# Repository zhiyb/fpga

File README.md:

# fpga
FPGA (DE0-Nano) attachment PCB designs for fun

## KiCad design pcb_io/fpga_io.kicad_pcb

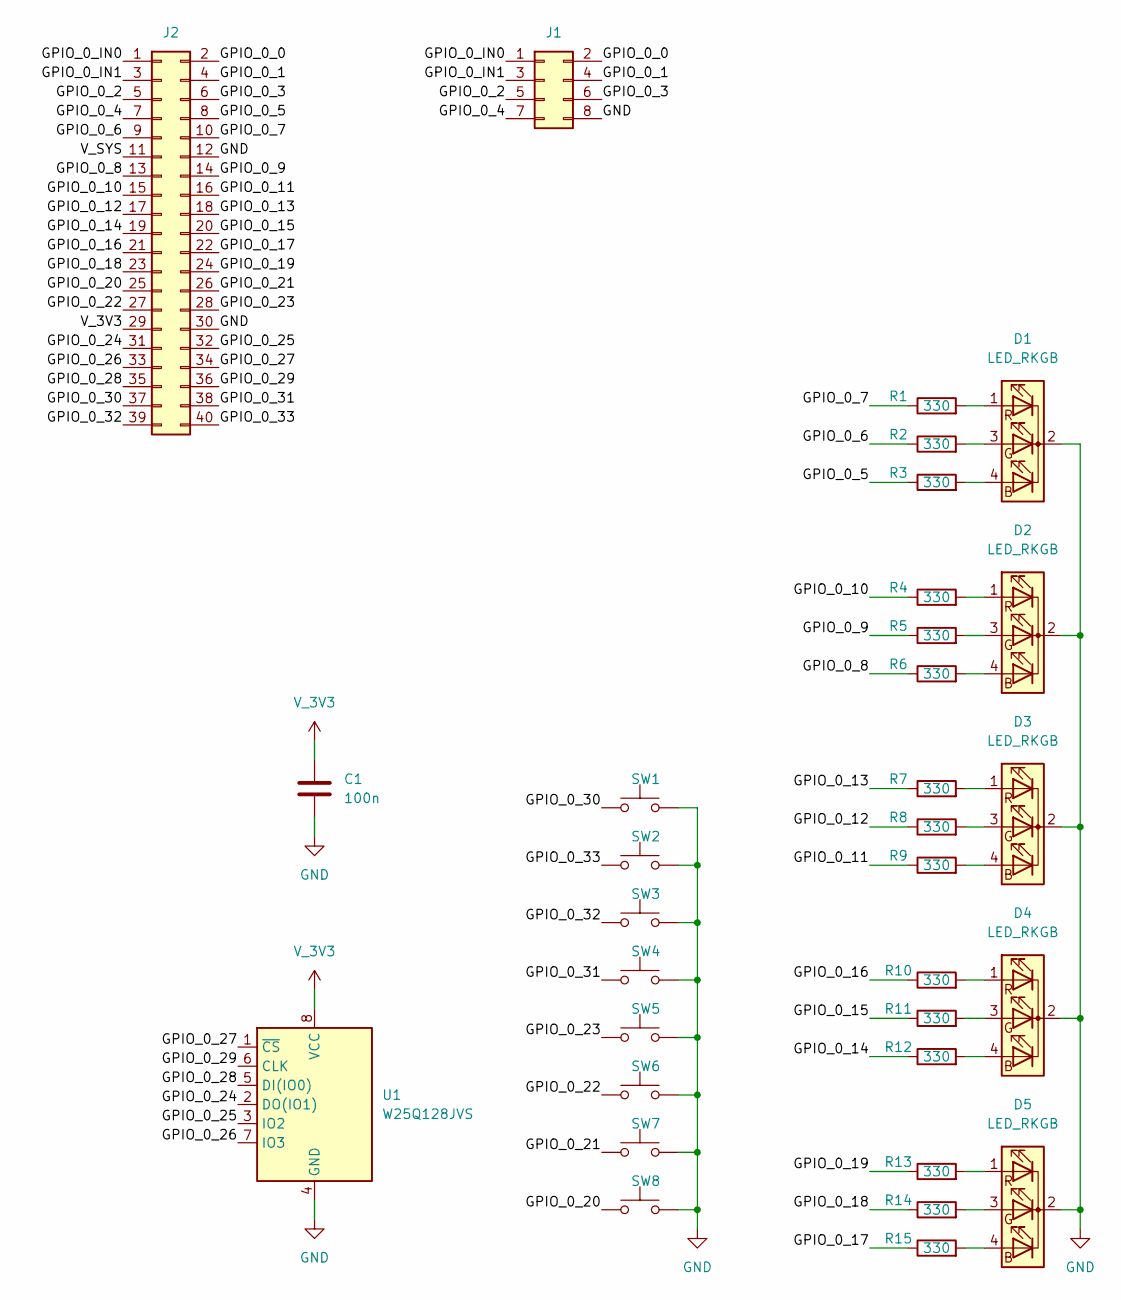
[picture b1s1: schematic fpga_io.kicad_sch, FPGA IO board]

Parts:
C1: 100n; C_0603_1608Metric
D1, D2, D3, D4, D5: LED_RKGB; LED_D5.0mm-4_RGB
J1: Conn_02x04_Odd_Even; PinHeader_2x04_P2.54mm_Vertical
J2: Conn_02x20_Odd_Even; PinSocket_2x20_P2.54mm_Vertical
R1, R2, R3, R4, R5, R6, R7, R8, R9, R10, R11, R12, R13, R14, R15: 330; R_0805_2012Metric
SW1, SW2, SW3, SW4, SW5, SW6, SW7, SW8: SW_Push; SW_Push_1P1T_NO_6x6mm_H9.5mm
U1: W25Q128JVS; SOIC-8_5.23x5.23mm_P1.27mm

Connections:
/GPIO_0_0: J1.2, J2.2
/GPIO_0_1: J1.4, J2.4
/GPIO_0_2: J1.5, J2.5
/GPIO_0_3: J1.6, J2.6
/GPIO_0_4: J1.7, J2.7
/GPIO_0_5: J2.8, R3.1
/GPIO_0_6: J2.9, R2.1
/GPIO_0_7: J2.10, R1.1
/GPIO_0_8: J2.13, R6.1
/GPIO_0_9: J2.14, R5.1
/GPIO_0_10: J2.15, R4.1
/GPIO_0_11: J2.16, R9.1
/GPIO_0_12: J2.17, R8.1
/GPIO_0_13: J2.18, R7.1
/GPIO_0_14: J2.19, R12.1
/GPIO_0_15: J2.20, R11.1
/GPIO_0_16: J2.21, R10.1
/GPIO_0_17: J2.22, R15.1
/GPIO_0_18: J2.23, R14.1
/GPIO_0_19: J2.24, R13.1
/GPIO_0_20: J2.25, SW8.1
/GPIO_0_21: J2.26, SW7.1
/GPIO_0_22: J2.27, SW6.1
/GPIO_0_23: J2.28, SW5.1
/GPIO_0_24: J2.31, U1.2 (DO(IO1))
/GPIO_0_25: J2.32, U1.3 (IO2)
/GPIO_0_26: J2.33, U1.7 (IO3)
/GPIO_0_27: J2.34, U1.1 (~CS)
/GPIO_0_28: J2.35, U1.5 (DI(IO0))
/GPIO_0_29: J2.36, U1.6 (CLK)
/GPIO_0_30: J2.37, SW1.1
/GPIO_0_31: J2.38, SW4.1
/GPIO_0_32: J2.39, SW3.1
/GPIO_0_33: J2.40, SW2.1
/GPIO_0_IN0: J1.1, J2.1
/GPIO_0_IN1: J1.3, J2.3
/V_SYS: J2.11
GND: C1.2, D1.2 (K), D2.2 (K), D3.2 (K), D4.2 (K), D5.2 (K), J1.8, J2.12, J2.30, SW1.2, SW2.2, SW3.2, SW4.2, SW5.2, SW6.2, SW7.2, SW8.2, U1.4 (GND)
unnamed: D1.4 (BA), R3.2
unnamed: D1.3 (GA), R2.2
unnamed: D1.1 (RA), R1.2
unnamed: D2.4 (BA), R6.2
unnamed: D2.3 (GA), R5.2
unnamed: D2.1 (RA), R4.2
unnamed: D3.4 (BA), R9.2
unnamed: D3.3 (GA), R8.2
unnamed: D3.1 (RA), R7.2
unnamed: D4.4 (BA), R12.2
unnamed: D4.3 (GA), R11.2
unnamed: D4.1 (RA), R10.2
unnamed: D5.4 (BA), R15.2
unnamed: D5.3 (GA), R14.2
unnamed: D5.1 (RA), R13.2
V_3V3: C1.1, J2.29, U1.8 (VCC)

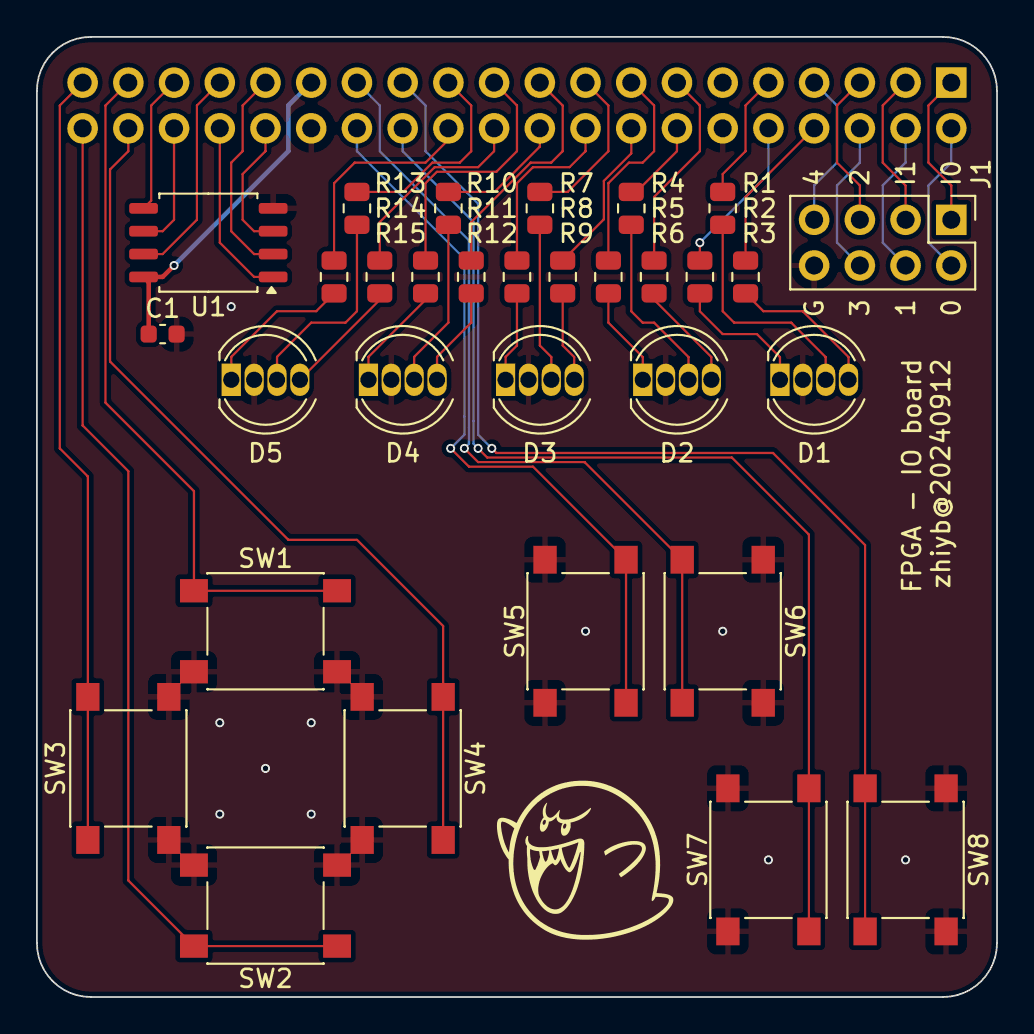
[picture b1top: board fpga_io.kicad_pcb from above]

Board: 2 copper layers, 53.3 x 53.3 mm, 32 parts (1 on the bottom side), 53 nets.

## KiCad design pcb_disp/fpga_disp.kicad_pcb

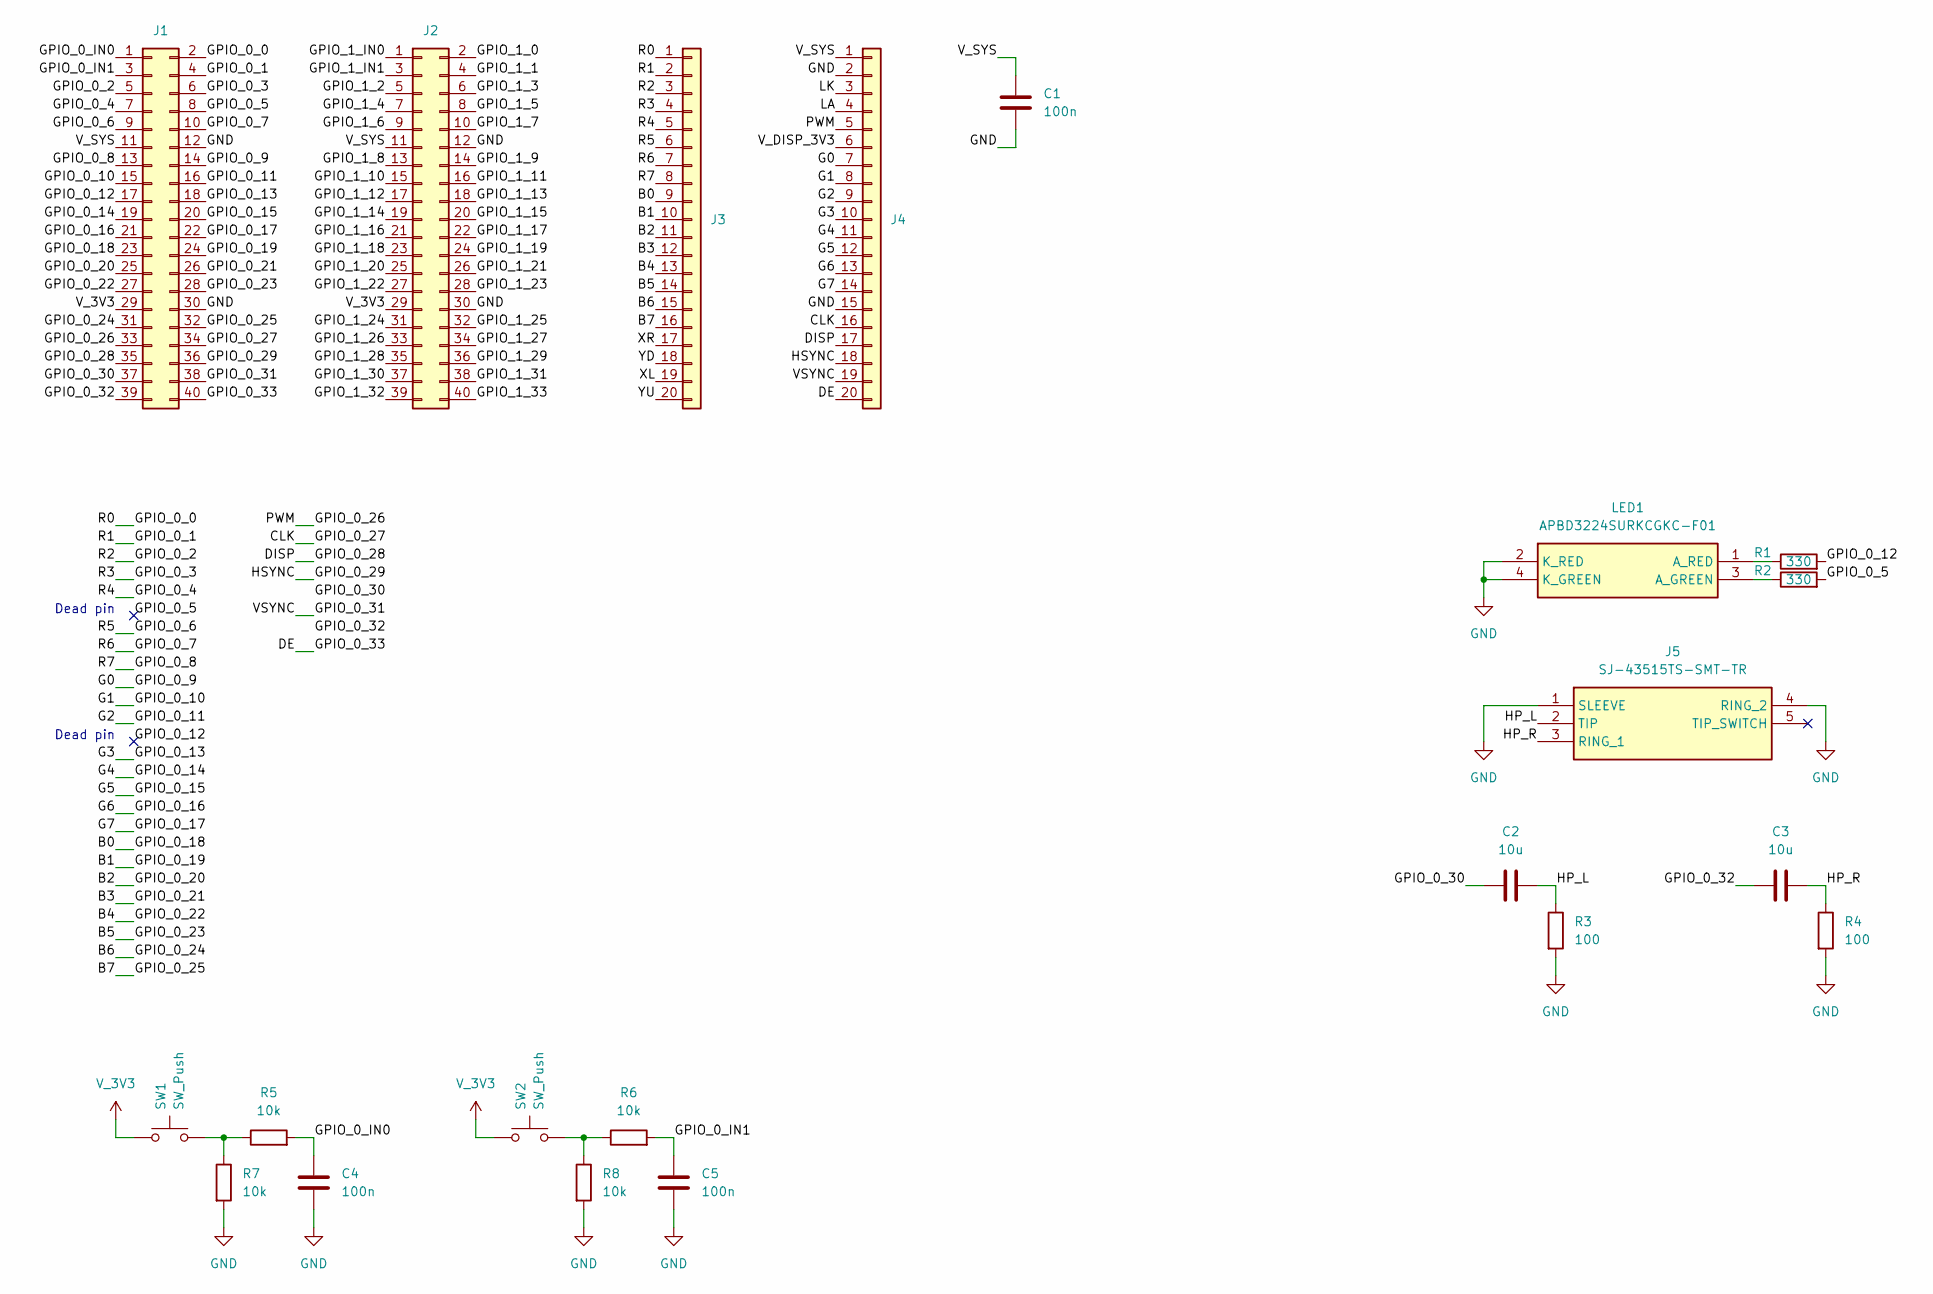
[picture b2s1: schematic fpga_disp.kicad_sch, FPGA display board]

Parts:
C1, C4, C5: 100n; C_0603_1608Metric
C2, C3: 10u; C_0805_2012Metric
J1, J2: Conn_02x20_Odd_Even; PinSocket_2x20_P2.54mm_Vertical
J3, J4: Conn_01x20; PinHeader_1x20_P2.54mm_Vertical
J5: SJ-43515TS-SMT-TR; SJ43515TSSMTTR; Mouser Part Number 490-SJ43515TS-SMT-TR
LED1: APBD3224SURKCGKC-F01; APBD3224SURKCGKCF01; Mouser Part Number 604-APBD3224SURKCGKC
R1, R2: 330; R_0805_2012Metric
R3, R4: 100; R_0805_2012Metric
R5, R6, R7, R8: 10k; R_0805_2012Metric
SW1, SW2: SW_Push; SW_Push_1P1T_NO_6x6mm_H9.5mm

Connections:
/B0: J1.23, J3.9
/B1: J1.24, J3.10
/B2: J1.25, J3.11
/B3: J1.26, J3.12
/B4: J1.27, J3.13
/B5: J1.28, J3.14
/B6: J1.31, J3.15
/B7: J1.32, J3.16
/CLK: J1.34, J4.16
/DE: J1.40, J4.20
/DISP: J1.35, J4.17
/G0: J1.14, J4.7
/G1: J1.15, J4.8
/G2: J1.16, J4.9
/G3: J1.18, J4.10
/G4: J1.19, J4.11
/G5: J1.20, J4.12
/G6: J1.21, J4.13
/G7: J1.22, J4.14
/GPIO_0_0: J1.2, J3.1
/GPIO_0_1: J1.4, J3.2
/GPIO_0_2: J1.5, J3.3
/GPIO_0_3: J1.6, J3.4
/GPIO_0_4: J1.7, J3.5
/GPIO_0_5: J1.8, R2.2
/GPIO_0_6: J1.9, J3.6
/GPIO_0_7: J1.10, J3.7
/GPIO_0_8: J1.13, J3.8
/GPIO_0_12: J1.17, R1.2
/GPIO_0_26: J1.33, J4.5
/GPIO_0_29: J1.36, J4.18
/GPIO_0_30: C2.1, J1.37
/GPIO_0_31: J1.38, J4.19
/GPIO_0_32: C3.1, J1.39
/GPIO_0_IN0: C4.1, J1.1, R5.2
/GPIO_0_IN1: C5.1, J1.3, R6.2
/HP_L: C2.2, J5.2 (TIP), R3.1
/HP_R: C3.2, J5.3 (RING_1), R4.1
/LA: J4.4
/LK: J4.3
/V_DISP_3V3: J4.6
/V_SYS: C1.1, J1.11, J2.11, J4.1
/XL: J3.19
/XR: J3.17
/YD: J3.18
/YU: J3.20
GND: C1.2, C4.2, C5.2, J1.12, J1.30, J2.12, J2.30, J4.2, J4.15, J5.1 (SLEEVE), J5.4 (RING_2), LED1.2 (K_RED), LED1.4 (K_GREEN), R3.2, R4.2, R7.2, R8.2
unnamed: LED1.3 (A_GREEN), R2.1
unnamed: LED1.1 (A_RED), R1.1
unnamed: R5.1, R7.1, SW1.2
unnamed: R6.1, R8.1, SW2.2
V_3V3: J1.29, J2.29, SW1.1, SW2.1

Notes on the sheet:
Dead pin

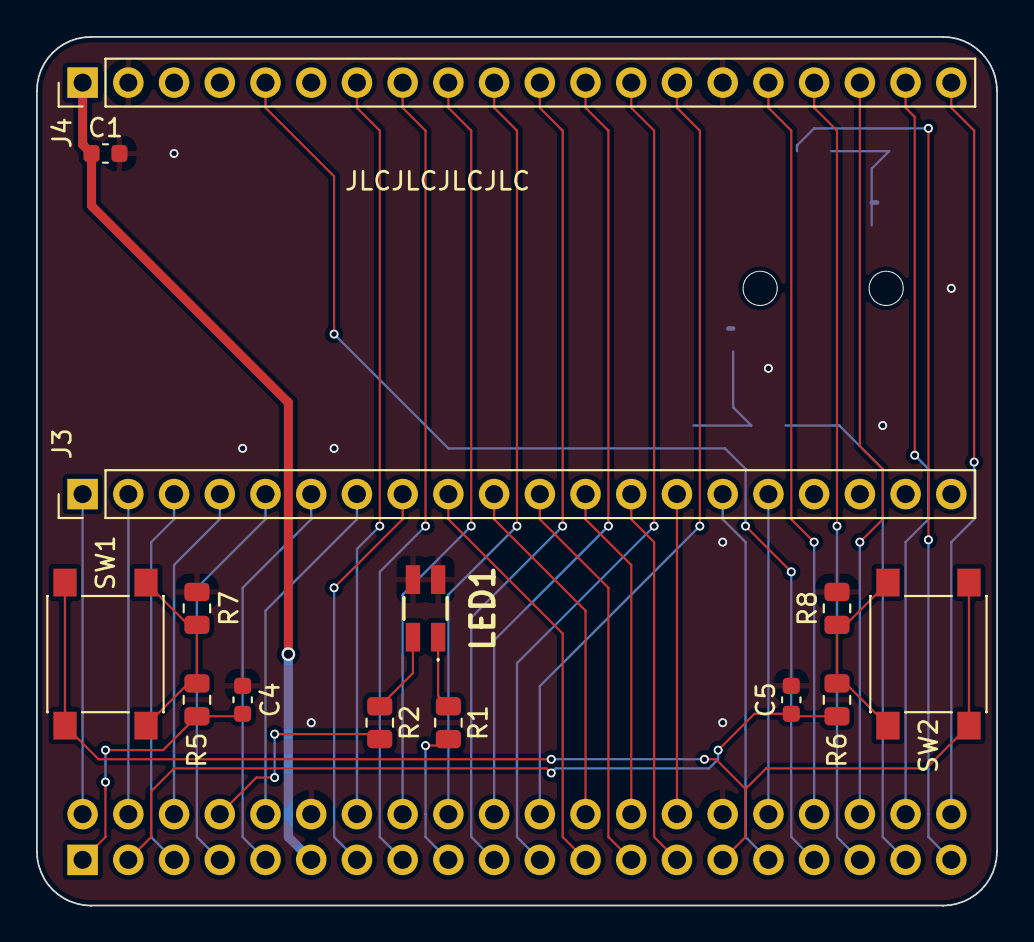
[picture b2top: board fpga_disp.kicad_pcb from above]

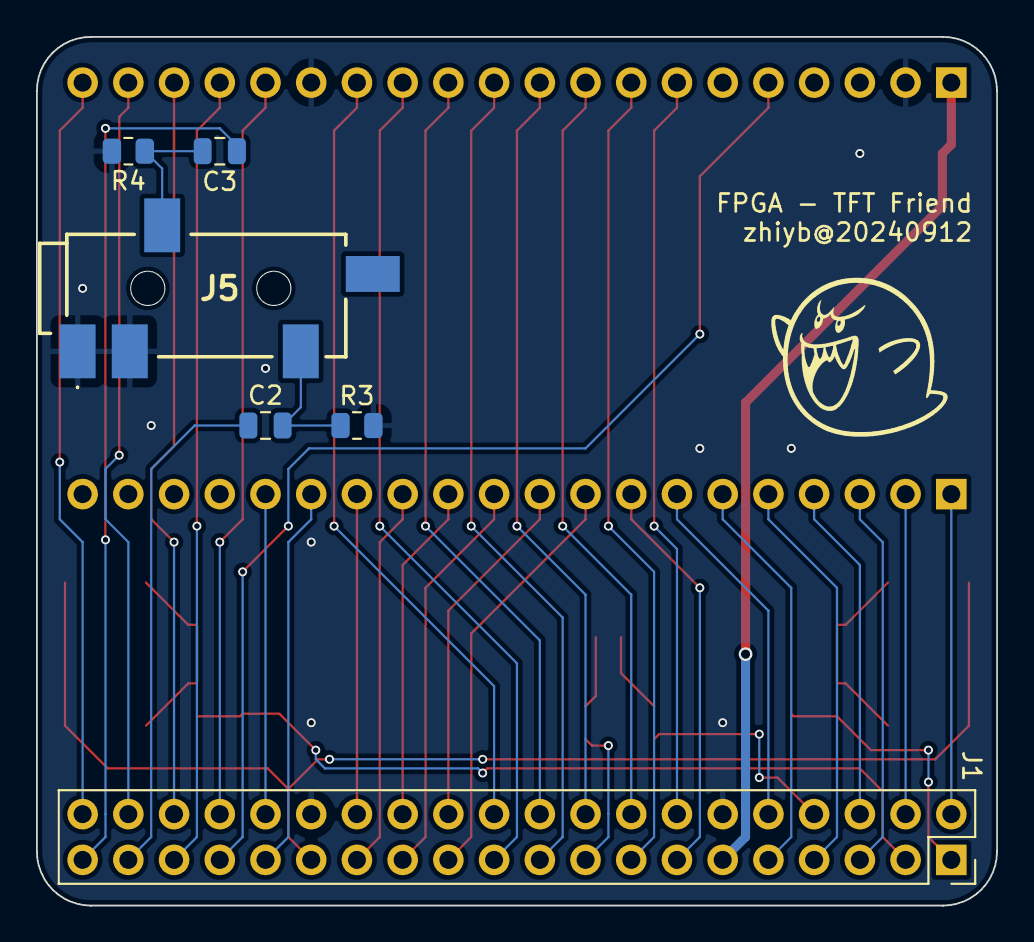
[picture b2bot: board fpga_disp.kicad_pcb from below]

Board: 2 copper layers, 53.3 x 48.3 mm, 20 parts (6 on the bottom side), 45 nets.

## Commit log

2024-09-13 pcb_disp: Version 20240912
2024-09-13 pcb_io: Version 20240912
